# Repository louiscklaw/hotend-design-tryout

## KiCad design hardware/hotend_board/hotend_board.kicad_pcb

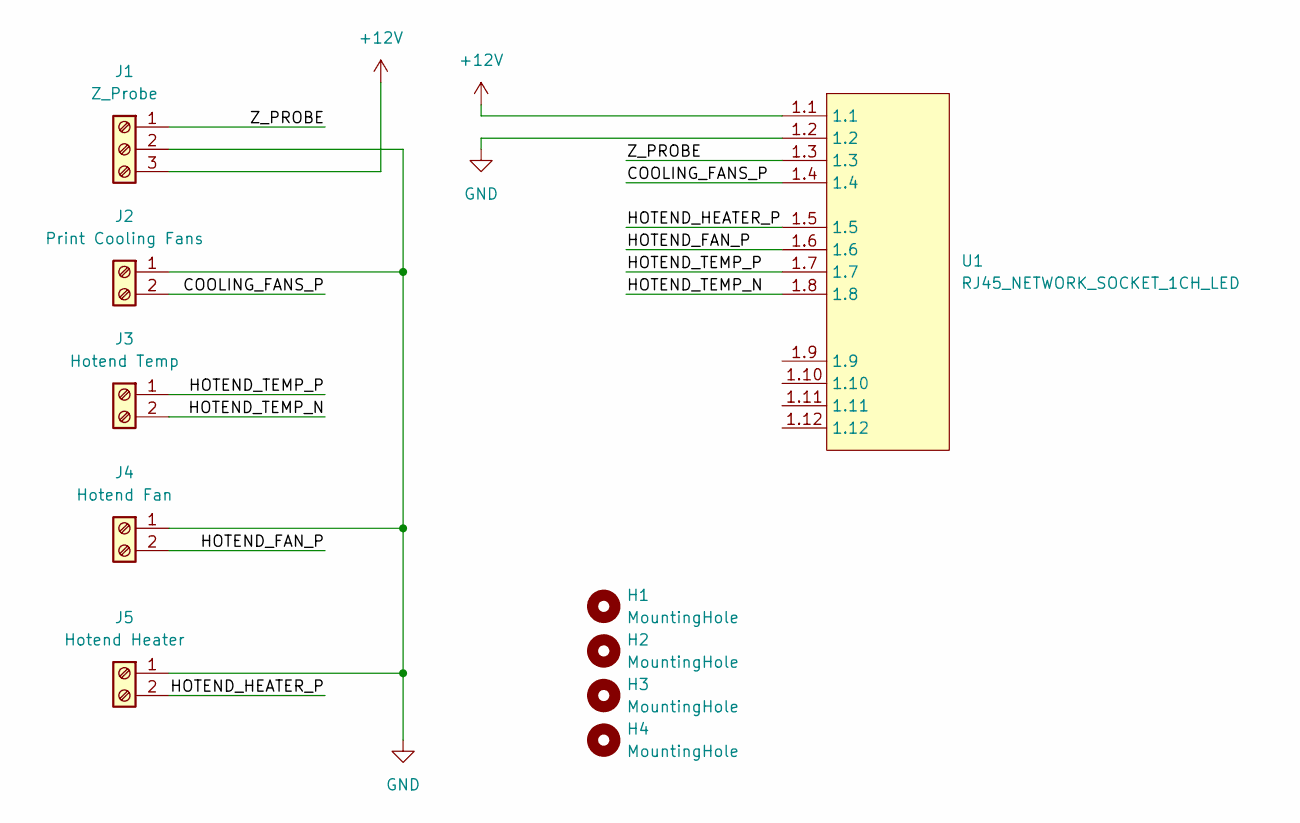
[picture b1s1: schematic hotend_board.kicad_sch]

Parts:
H1, H2, H3, H4: MountingHole; MountingHole_3.1mm_M3,rpi_like
J1: Z_Probe; PhoenixContact_MCV_1,5_3-G-5.08_1x03_P5.08mm_Vertical
J2: Print Cooling Fans; PhoenixContact_MCV_1,5_2-G-3.81_1x02_P3.81mm_Vertical
J3: Hotend Temp; PhoenixContact_MCV_1,5_2-G-3.81_1x02_P3.81mm_Vertical
J4: Hotend Fan; PhoenixContact_MCV_1,5_2-G-3.81_1x02_P3.81mm_Vertical
J5: Hotend Heater; PhoenixContact_MCV_1,5_2-G-3.81_1x02_P3.81mm_Vertical
U1: RJ45_NETWORK_SOCKET_1CH_LED; RJ45_NETWORK_SOCKET_1CH_1_VERTICAL

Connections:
+12V: J1.3, U1.1.1
/COOLING_FANS_P: J2.2, U1.1.4
/HOTEND_FAN_P: J4.2, U1.1.6
/HOTEND_HEATER_P: J5.2, U1.1.5
/HOTEND_TEMP_N: J3.2, U1.1.8
/HOTEND_TEMP_P: J3.1, U1.1.7
/Z_PROBE: J1.1, U1.1.3
GND: J1.2, J2.1, J4.1, J5.1, U1.1.2

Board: 2 copper layers, 10 parts (0 on the bottom side), 8 nets, no tracks yet.

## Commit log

2020-05-05 ci: init travis token,
2020-05-05 ci: init travis build config,
2022-02-03 update,
